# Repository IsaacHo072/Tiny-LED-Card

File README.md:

# Tiny LED Card
 A tiny credit card sized LED light

# Hardware
 Currently using 3030 LED and TPS61165 driver.
 
 Update 2022 Feb: It seems that you can't buy the TPS61165 anymore, all places are out of stock. 
 
 Update 2023: TPS61165 back in stock in most marketplace

## 3030 LED
 Luminus Device MP3030-110H
 
 Nominal: 3V 65mA
 
 Maximum: 200mA

## TPS61165
 Boost converter for LEDs in series

 Input voltage: 3-18V
 
 1.2A current limit

## PCB
 Aluminium PCB, single layer, for LED.
 
 FR-4 PCB, Two layers, for driver.
 Components on single side for easy assembly.
 
 2 PCBs connected with 2.54mm headers for upgradability 

## Enclosure
 3D Printed with PLA or any filament
 
 Screws: 4x M3x20
 
 2x M3x12-16mm 
 
# Assembly
 See the BOM for parts.
 Total cost should be under $25

 For the Aluminium PCB, you need a hotplate or a beefy hotair gun.
 It is impossible to solder with a soldering iron 
 
 For the driver PCB, any soldering iron will work, hotplate would also work well.
 
 R1 and R2 are the sense resistor for the LED driver, use the following resistor: 
  for other current see the datasheet of TPS61165
 
 | Resistor (Ω)  | LED Current (each) | Power | 
| ------------- | ------------- | ------------- |
| 1  | 50mA  | 14.4W |
| 0.5  | 100mA  | 28.8W |
| 0.33  | 150mA  | 43.2W |
| 0.25  | 200mA  | 57.6W |

 For the enclosure, print each file once and screw them together.
 
 Glue a heatsink with thermal adhesive at the back of the aluminium PCB after checked working.

## Usage
 Plug a 12V DC power supply in, light will come out from the bright side.
 
 It is not advised to use the Micro USB for power as a large amperage will be needed at 5V. Also, having both accidentally plugged in will damage the Micro USB device.

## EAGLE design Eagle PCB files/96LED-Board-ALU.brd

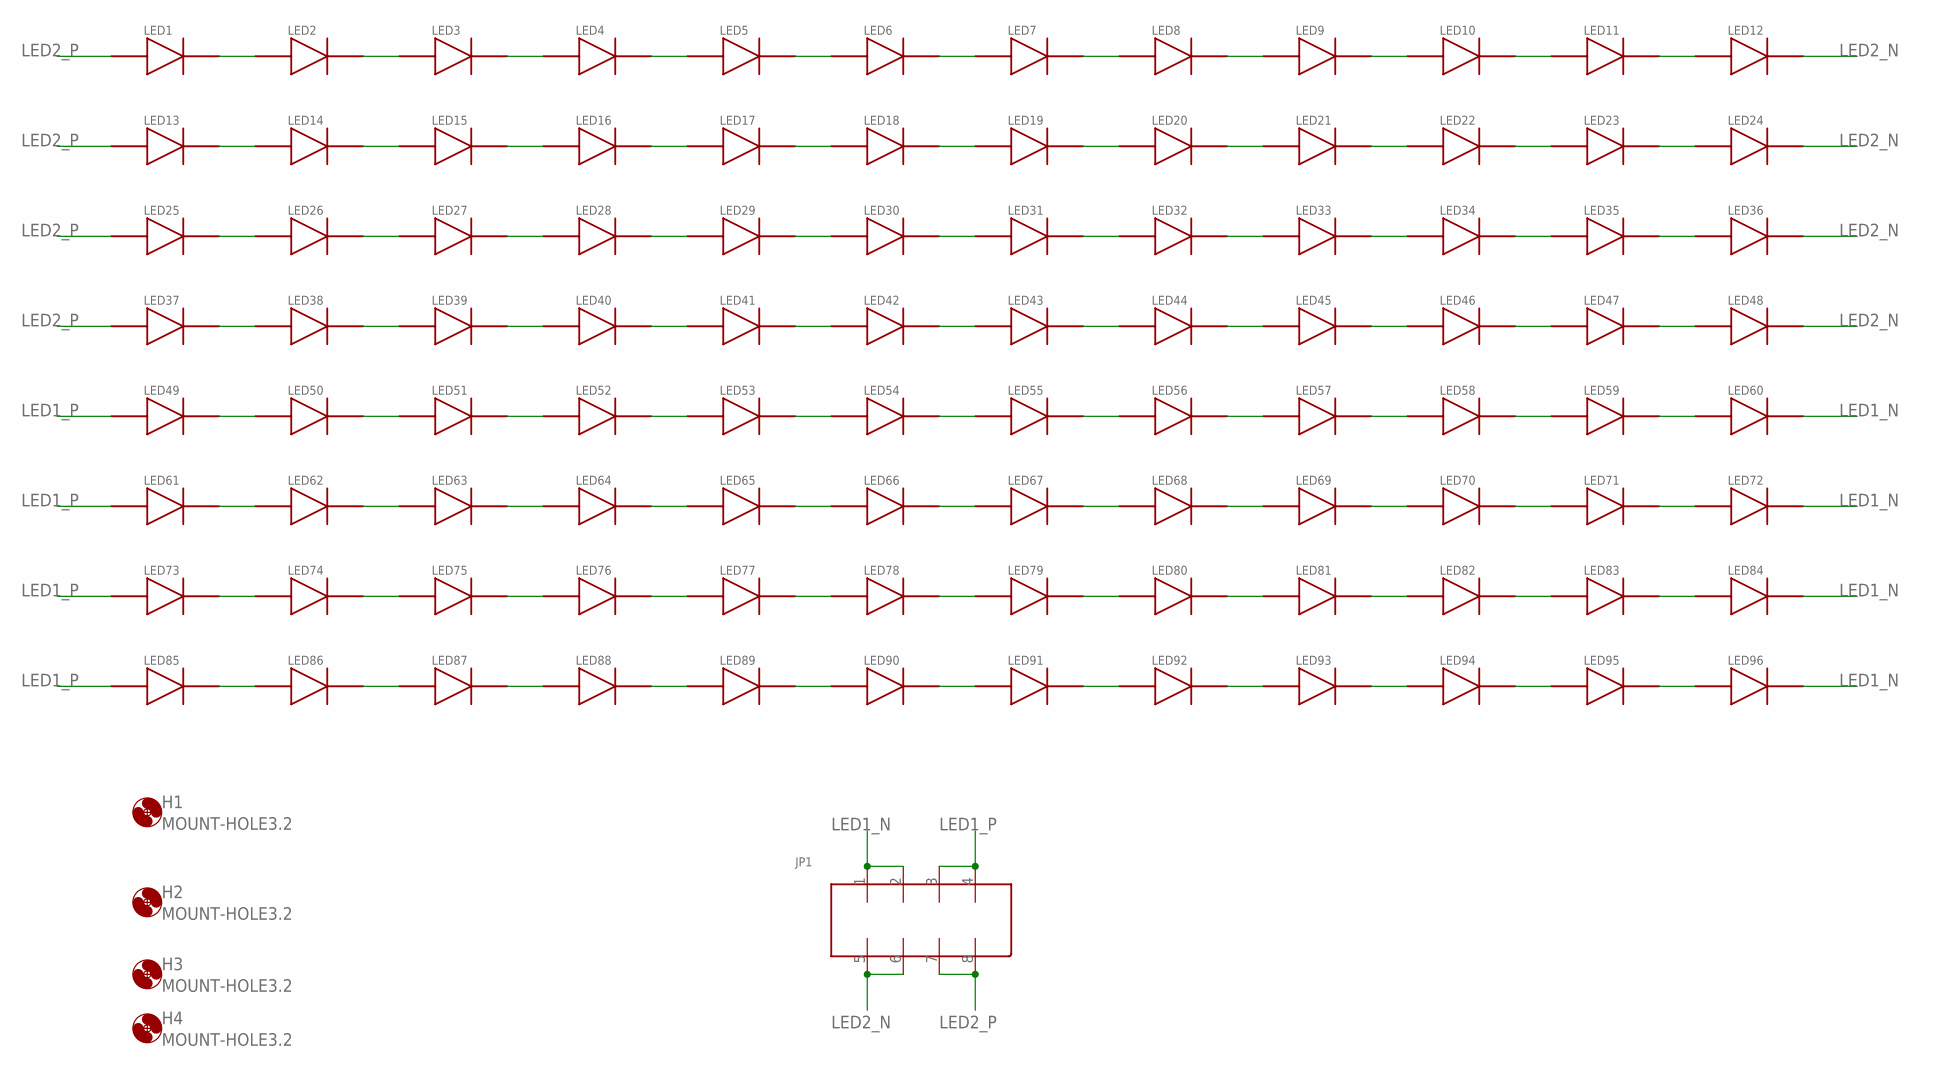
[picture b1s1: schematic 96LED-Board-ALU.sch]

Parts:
H1, H2, H3, H4: MOUNT-HOLE3.2; 3,2
JP1: 2X8P_2.54_FEMALE; 2X8_PIN_SMD_2.54-FEMALE
LED1, LED2, LED3, LED4, LED5, LED6, LED7, LED8, LED9, LED10, LED11, LED12, LED13, LED14, LED15, LED16, LED17, LED18, LED19, LED20, LED21, LED22, LED23, LED24, LED25, LED26, LED27, LED28, LED29, LED30, LED31, LED32, LED33, LED34, LED35, LED36, LED37, LED38, LED39, LED40, LED41, LED42, LED43, LED44, LED45, LED46, LED47, LED48, LED49, LED50, LED51, LED52, LED53, LED54, LED55, LED56, LED57, LED58, LED59, LED60, LED61, LED62, LED63, LED64, LED65, LED66, LED67, LED68, LED69, LED70, LED71, LED72, LED73, LED74, LED75, LED76, LED77, LED78, LED79, LED80, LED81, LED82, LED83, LED84, LED85, LED86, LED87, LED88, LED89, LED90, LED91, LED92, LED93, LED94, LED95, LED96: MP3030_N

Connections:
LED1_N: JP1.1, JP1.2, LED60.2, LED72.2, LED84.2, LED96.2
LED1_P: JP1.3, JP1.4, LED49.1, LED61.1, LED73.1, LED85.1
LED2_N: JP1.5, JP1.6, LED12.2, LED24.2, LED36.2, LED48.2
LED2_P: JP1.7, JP1.8, LED1.1, LED13.1, LED25.1, LED37.1
unnamed: LED1.2, LED2.1
unnamed: LED2.2, LED3.1
unnamed: LED3.2, LED4.1
unnamed: LED4.2, LED5.1
unnamed: LED5.2, LED6.1
unnamed: LED6.2, LED7.1
unnamed: LED7.2, LED8.1
unnamed: LED8.2, LED9.1
unnamed: LED9.2, LED10.1
unnamed: LED10.2, LED11.1
unnamed: LED11.2, LED12.1
unnamed: LED13.2, LED14.1
unnamed: LED14.2, LED15.1
unnamed: LED15.2, LED16.1
unnamed: LED16.2, LED17.1
unnamed: LED17.2, LED18.1
unnamed: LED18.2, LED19.1
unnamed: LED19.2, LED20.1
unnamed: LED20.2, LED21.1
unnamed: LED21.2, LED22.1
unnamed: LED22.2, LED23.1
unnamed: LED23.2, LED24.1
unnamed: LED25.2, LED26.1
unnamed: LED26.2, LED27.1
unnamed: LED27.2, LED28.1
unnamed: LED28.2, LED29.1
unnamed: LED29.2, LED30.1
unnamed: LED30.2, LED31.1
unnamed: LED31.2, LED32.1
unnamed: LED32.2, LED33.1
unnamed: LED33.2, LED34.1
unnamed: LED34.2, LED35.1
unnamed: LED35.2, LED36.1
unnamed: LED37.2, LED38.1
unnamed: LED38.2, LED39.1
unnamed: LED39.2, LED40.1
unnamed: LED40.2, LED41.1
unnamed: LED41.2, LED42.1
unnamed: LED42.2, LED43.1
unnamed: LED43.2, LED44.1
unnamed: LED44.2, LED45.1
unnamed: LED45.2, LED46.1
unnamed: LED46.2, LED47.1
unnamed: LED47.2, LED48.1
unnamed: LED49.2, LED50.1
unnamed: LED50.2, LED51.1
unnamed: LED51.2, LED52.1
unnamed: LED52.2, LED53.1
unnamed: LED53.2, LED54.1
unnamed: LED54.2, LED55.1
unnamed: LED55.2, LED56.1
unnamed: LED56.2, LED57.1
unnamed: LED57.2, LED58.1
unnamed: LED58.2, LED59.1
unnamed: LED59.2, LED60.1
unnamed: LED61.2, LED62.1
unnamed: LED62.2, LED63.1
unnamed: LED63.2, LED64.1
unnamed: LED64.2, LED65.1
unnamed: LED65.2, LED66.1
unnamed: LED66.2, LED67.1
unnamed: LED67.2, LED68.1
unnamed: LED68.2, LED69.1
unnamed: LED69.2, LED70.1
unnamed: LED70.2, LED71.1
unnamed: LED71.2, LED72.1
unnamed: LED73.2, LED74.1
unnamed: LED74.2, LED75.1
unnamed: LED75.2, LED76.1
unnamed: LED76.2, LED77.1
unnamed: LED77.2, LED78.1
unnamed: LED78.2, LED79.1
unnamed: LED79.2, LED80.1
unnamed: LED80.2, LED81.1
unnamed: LED81.2, LED82.1
unnamed: LED82.2, LED83.1
unnamed: LED83.2, LED84.1
unnamed: LED85.2, LED86.1
unnamed: LED86.2, LED87.1
unnamed: LED87.2, LED88.1
unnamed: LED88.2, LED89.1
unnamed: LED89.2, LED90.1
unnamed: LED90.2, LED91.1
unnamed: LED91.2, LED92.1
unnamed: LED92.2, LED93.1
unnamed: LED93.2, LED94.1
unnamed: LED94.2, LED95.1
unnamed: LED95.2, LED96.1

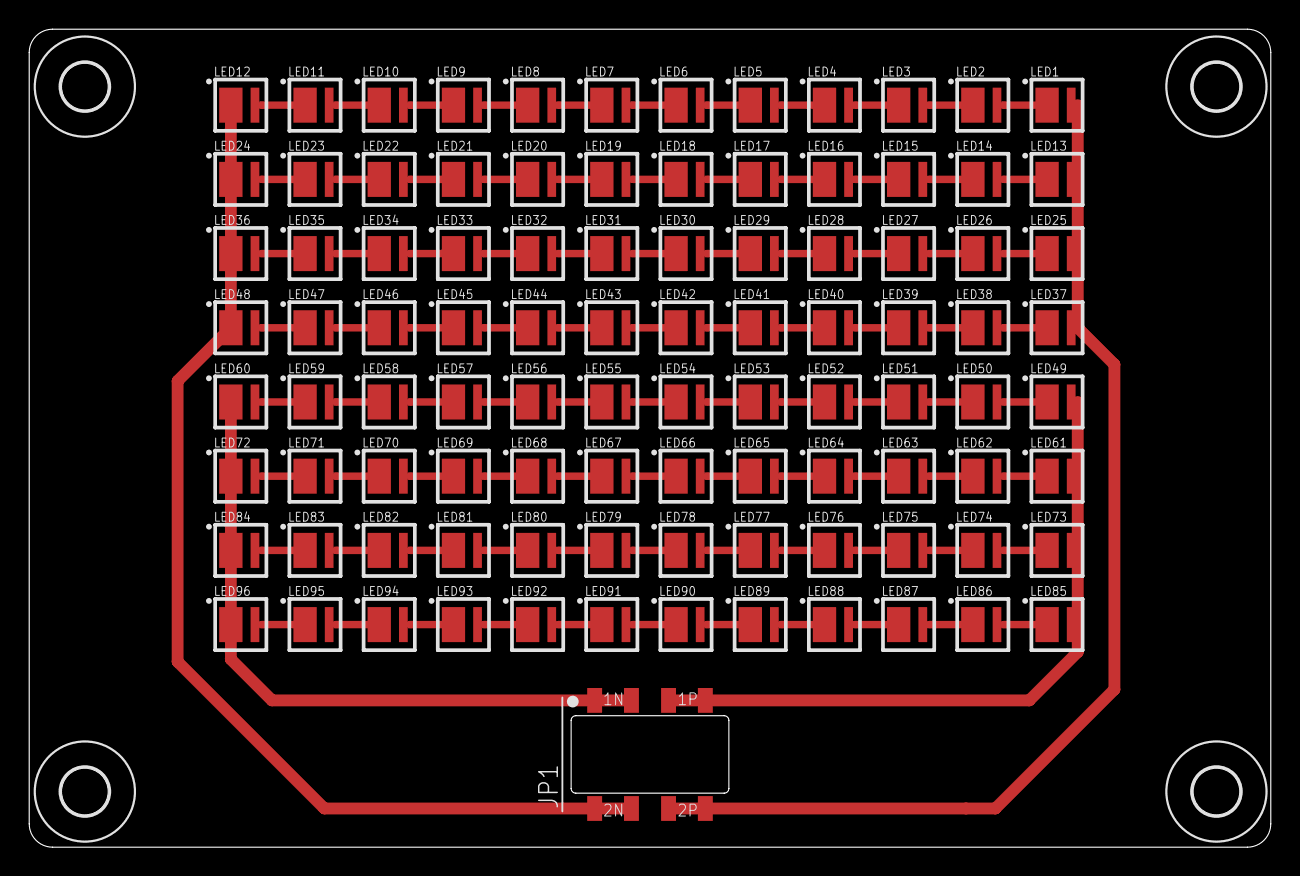
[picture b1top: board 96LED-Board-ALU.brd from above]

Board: 2 copper layers, 85.0 x 56.0 mm, 101 parts (0 on the bottom side), 92 nets.

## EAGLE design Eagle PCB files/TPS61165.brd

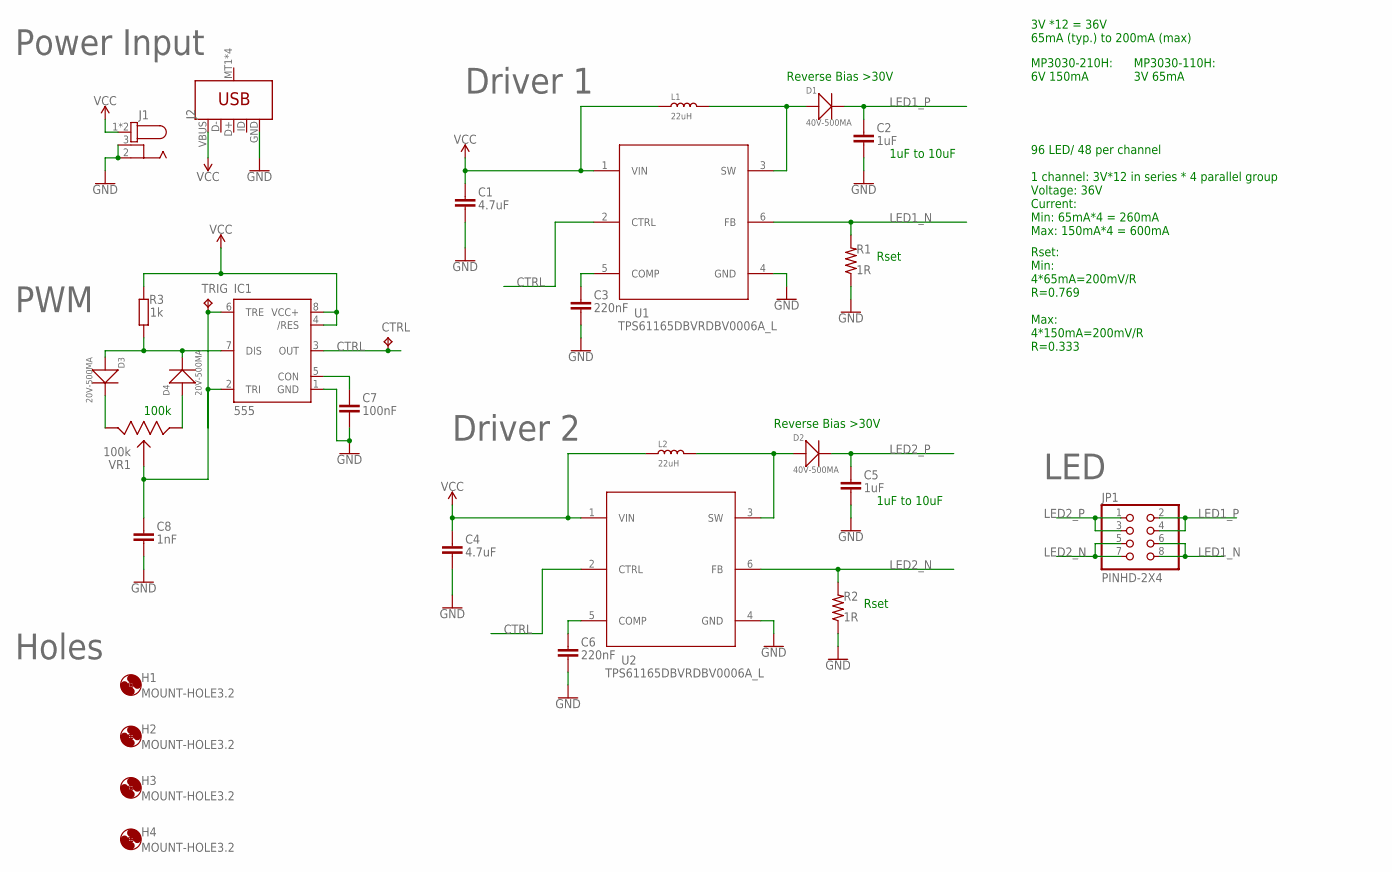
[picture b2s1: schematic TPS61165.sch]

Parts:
C1, C4: 4.7uF; CAPC2012X110
C2, C5: 1uF; CAPC2012X110
C3, C6: 220nF; CAPC1608X85
C7: 100nF; CAPC1608X85
C8: 1nF; CAPC1608X85
CTRL: TPB1,27; B1,27
D1, D2: 40V-500MA; SOD-123
D3, D4: 20V-500MA; SOD-123
H1, H2, H3, H4: MOUNT-HOLE3.2; 3,2
IC1: 555; SO08
J1: 694108106102
J2: USB_MICRO-B_SMT; USB-MICROB
JP1: PINHD-2X4; 2X04
L1, L2: 22uH; SMD-2P-L6.0XW6.0XH3.0MM
R1, R2: 1R; RESC3216X70
R3: 1k; RESC1608X60
TRIG: TPB1,27; B1,27
U1, U2: TPS61165DBVRDBV0006A_L; DBV0006A_L
VR1: 100k; B104-5PIN

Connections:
COMP: C3.1, U1.5 (COMP)
COMP1: C6.1, U2.5 (COMP)
CON: C7.1, IC1.5 (CON)
CTRL: CTRL.TP, IC1.3 (OUT), U1.2 (CTRL), U2.2 (CTRL)
DISCHARGE: D3.+, D4.-, IC1.7 (DIS), R3.1
GND: C1.2, C2.2, C3.2, C4.2, C5.2, C6.2, C7.2, C8.2, IC1.1 (GND), J1.2, J1.3, J2.GND, R1.1, R2.1, U1.4 (GND), U2.4 (GND)
LED1_N: JP1.6, JP1.8, R1.2, U1.6 (FB)
LED1_P: C2.1, D1.-, JP1.2, JP1.4
LED2_N: JP1.5, JP1.7, R2.2, U2.6 (FB)
LED2_P: C5.1, D2.-, JP1.1, JP1.3
unnamed: D3.-, VR1.P$3
unnamed: D4.+, VR1.P$1
SW: D1.+, L1.2, U1.3 (SW)
SW1: D2.+, L2.2, U2.3 (SW)
TRIGGER: C8.1, IC1.2 (TRI), IC1.6 (TRE), TRIG.TP, VR1.NOT_P$2
VCC: C1.1, C4.1, IC1.4 (/RES), IC1.8 (VCC+), J1.1, J1.A1 (1), J2.VBUS, L1.1, L2.1, R3.2, U1.1 (VIN), U2.1 (VIN)

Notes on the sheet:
MP3030-210H: 6V 150mA
MP3030-110H: 3V 65mA
Rset
1uF to 10uF
Reverse Bias >30V
3V *12 = 36V 65mA (typ.) to 200mA (max)
100k
Power Input
PWM
Driver 1
Driver 2
Holes
Rset: Min: 4*65mA=200mV/R R=0.769 Max: 4*150mA=200mV/R R=0.333
96 LED/ 48 per channel 1 channel: 3V*12 in series * 4 parallel group Voltage: 36V Current: Min: 65mA*4 = 260mA Max: 150mA*4 = 600mA
LED

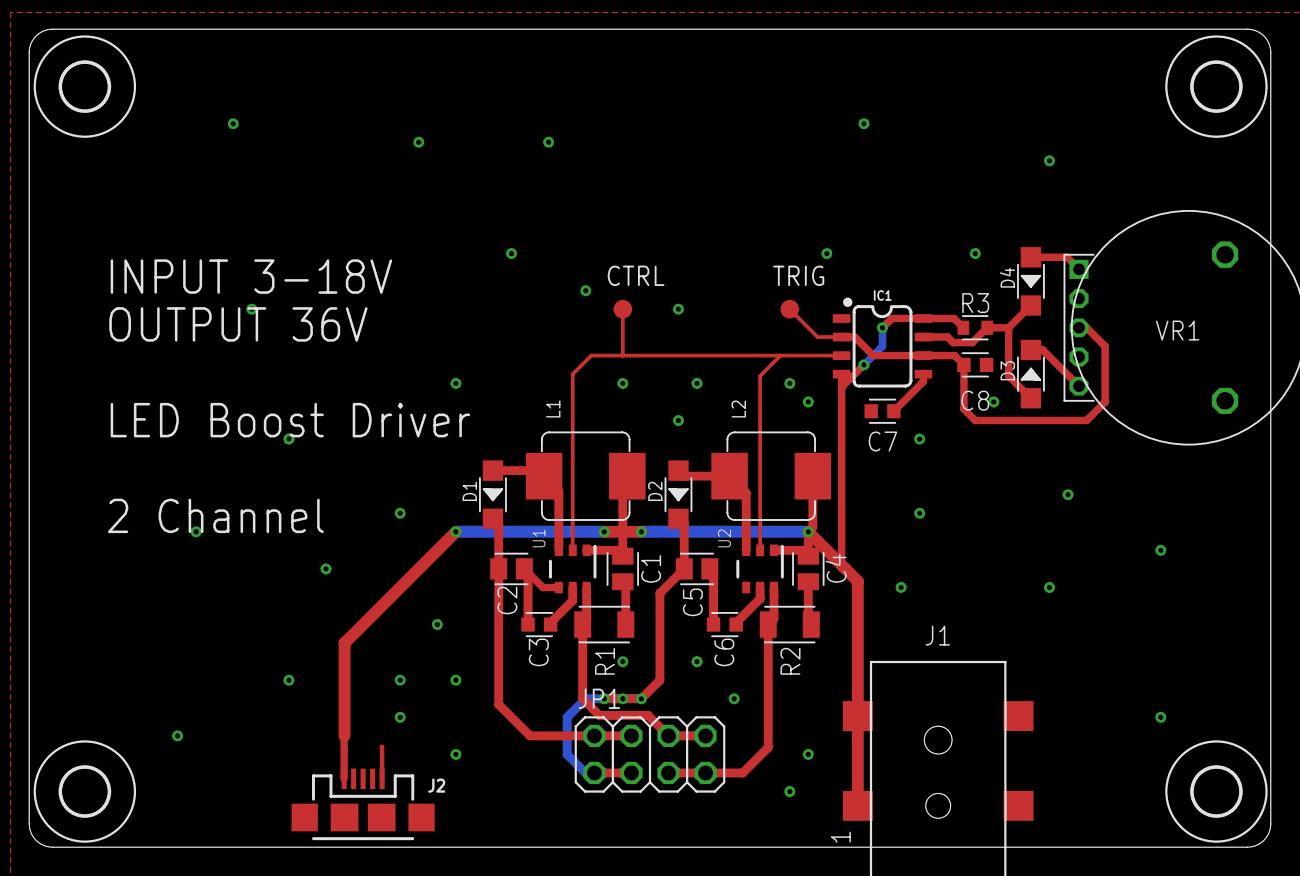
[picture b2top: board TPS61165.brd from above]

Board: 2 copper layers, 85.0 x 56.0 mm, 30 parts (0 on the bottom side), 16 nets.

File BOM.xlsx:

BOM
Driver
Part | Value | Package | CATEGORY | Remarks
C1 | 4.7uF | 0805 | Capacitor
C2 | 1uF | 0805 | Capacitor
C3 | 220nF | 0603 | Capacitor
C4 | 4.7uF | 0805 | Capacitor
C5 | 1uF | 0805 | Capacitor
C6 | 220nF | 0603 | Capacitor
C7 | 100nF | 0603 | Capacitor
C8 | 1nF | 0603 | Capacitor
D1 | 40V-500MA | SOD-123 | Diode
D2 | 40V-500MA | SOD-123 | Diode
D3 | 40V-500MA | SOD-123 | Diode
D4 | 40V-500MA | SOD-123 | Diode
H1 | MOUNT-HOLE3.2 | MOUNT-HOLE3.2 | Hole
H2 | MOUNT-HOLE3.2 | MOUNT-HOLE3.2 | Hole
H3 | MOUNT-HOLE3.2 | MOUNT-HOLE3.2 | Hole
H4 | MOUNT-HOLE3.2 | MOUNT-HOLE3.2 | Hole
IC1 | NE555 | SO08 | IC
J1 | DC5525 | SMD DC Power Jack | Connector
J2 |  | USB_MICRO-B_SMT |  | Not used
JP1 | PINHD-2X4 | PINHD-2X4 | Connector
L1 | 22uH | SMD-2P-L6.0XW6.0XH3.0MM
L2 | 22uH | SMD-2P-L6.0XW6.0XH3.0MM
R1 | 1R | 1206 | Resistor | Rset
R2 | 1R | 1206 | Resistor | Rset
R3 | 1k | 0603 | Resistor
U1 | TPS61165DBVR | SOT-23 | IC
U2 | TPS61165DBVR | SOT-23 | IC
VR1 | 100k | B104 (100K) 3 Pins | potentiometer
LED Board
LED1-96 | MP3030-110H | MP3030 | LED | Any 3V MP3030 LED could work
JP1 |  | SMD 2x4 | Connector | Sand the corners if it doesn’t fit

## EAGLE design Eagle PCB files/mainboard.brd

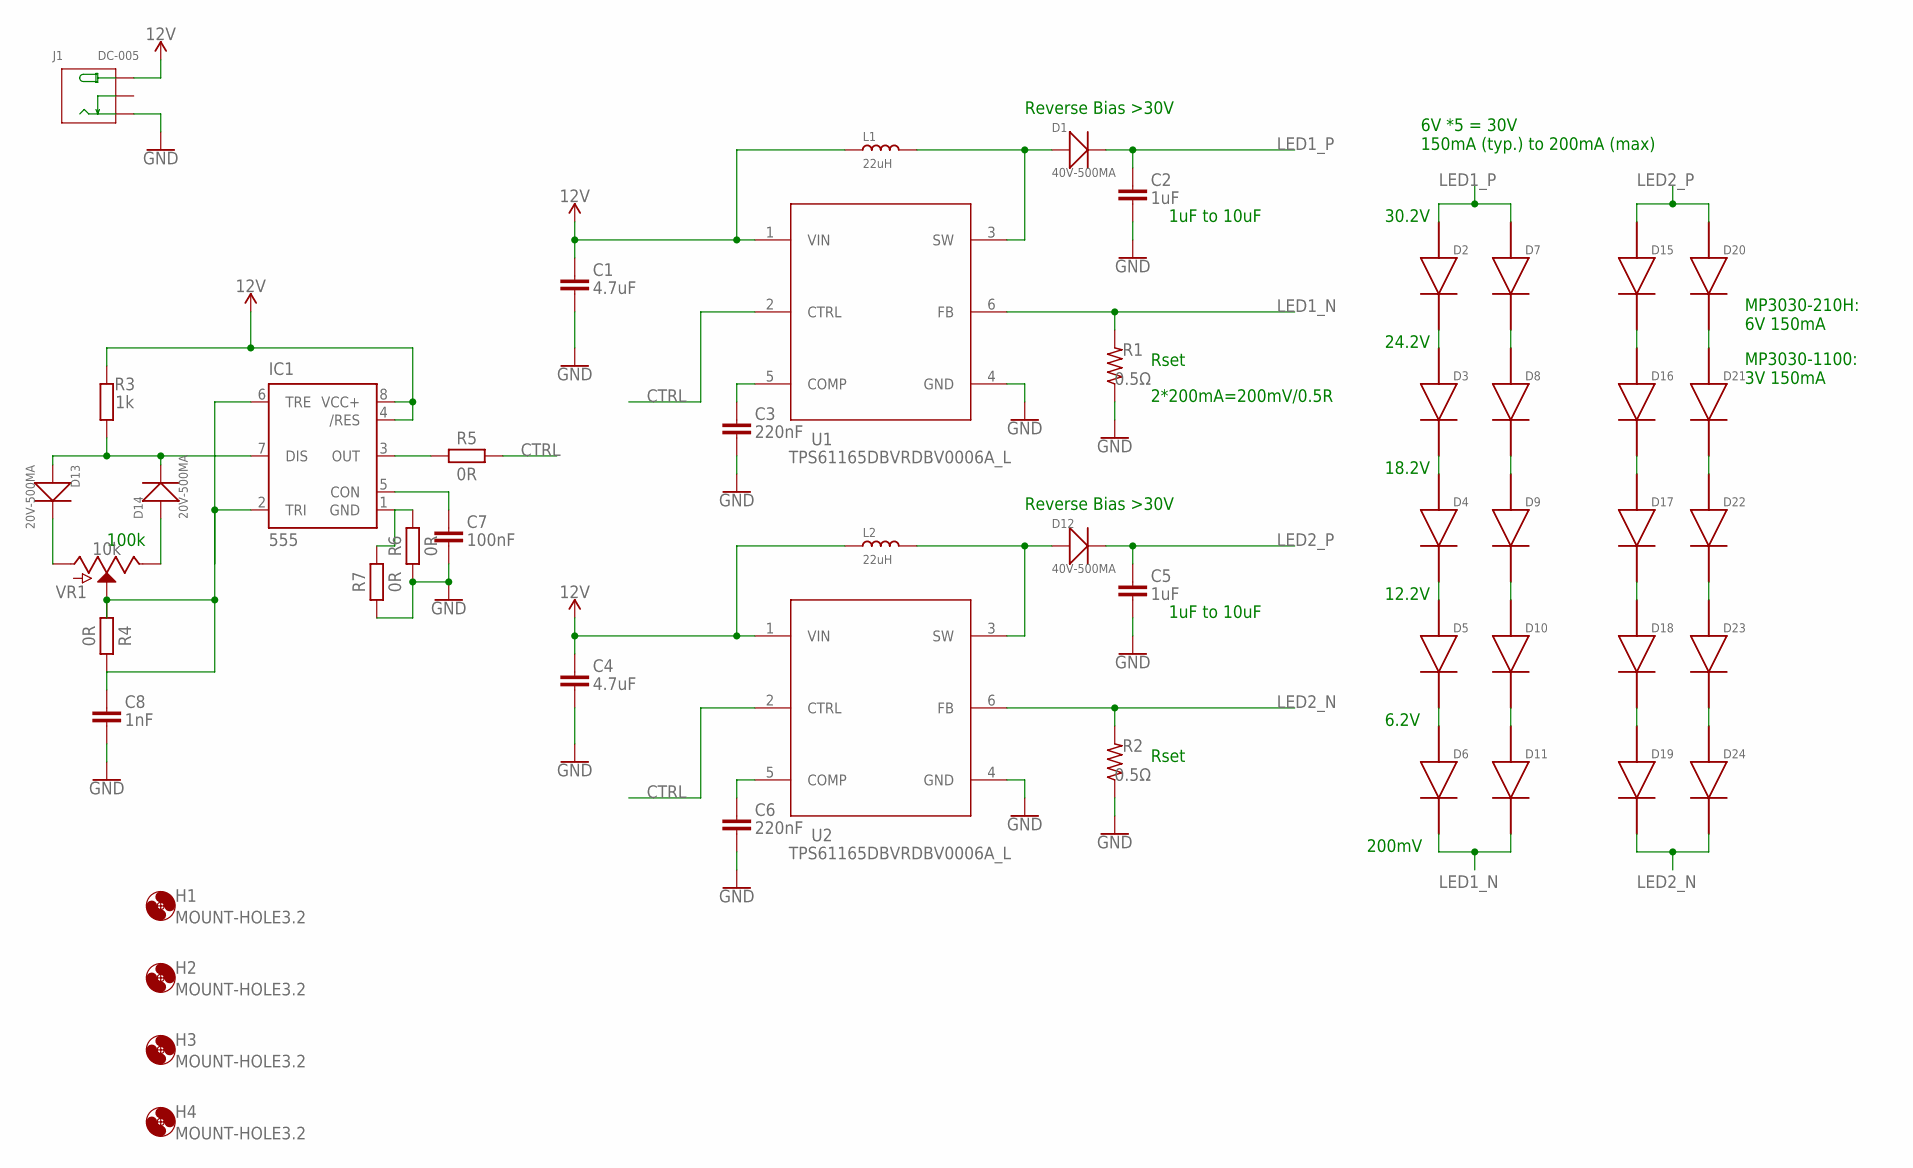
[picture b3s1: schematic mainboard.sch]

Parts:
C1, C4: 4.7uF; CAPC2012X110
C2, C5: 1uF; CAPC2012X110
C3, C6: 220nF; CAPC1608X85
C7: 100nF; CAPC1608X85
C8: 1nF; CAPC1608X85
D1, D12: 40V-500MA; SOD-123
D2, D3, D4, D5, D6, D7, D8, D9, D10, D11, D15, D16, D17, D18, D19, D20, D21, D22, D23, D24: MP3030_N
D13, D14: 20V-500MA; SOD-123
H1, H2, H3, H4: MOUNT-HOLE3.2; 3,2
IC1: 555; SO08
J1: DC-005; DCJ3P-14.2X11.0X9.0MM
L1, L2: 22uH; SMD-2P-L6.0XW6.0XH3.0MM
R1, R2: 0.5Ω; RESC3216X70
R3: 1k; RESC1608X60
R4, R5: 0R; RESC1608X60
R6, R7: 0R; RESC3216X70
U1, U2: TPS61165DBVRDBV0006A_L; DBV0006A_L
VR1: 10k; POT-PTH-ALPS

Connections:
12V: C1.1, C4.1, IC1.4 (/RES), IC1.8 (VCC+), J1.+B (+), J1.+T (+), L1.1, L2.1, R3.2, U1.1 (VIN), U2.1 (VIN)
COMP: C3.1, U1.5 (COMP)
COMP1: C6.1, U2.5 (COMP)
CON: C7.1, IC1.5 (CON)
CTRL: R5.2, U1.2 (CTRL), U2.2 (CTRL)
DISCHARGE: D13.+, D14.-, IC1.7 (DIS), R3.1
GND: C1.2, C2.2, C3.2, C4.2, C5.2, C6.2, C7.2, C8.2, IC1.1 (GND), J1.-1B (-), J1.-1T (-), R1.1, R2.1, R6.1, R6.2, R7.1, R7.2, U1.4 (GND), U2.4 (GND)
LED1_N: D6.2, D11.2, R1.2, U1.6 (FB)
LED1_P: C2.1, D1.-, D2.1, D7.1
LED2_N: D19.2, D24.2, R2.2, U2.6 (FB)
LED2_P: C5.1, D12.-, D15.1, D20.1
unnamed: D17.2, D18.1
unnamed: D2.2, D3.1
unnamed: D7.2, D8.1
unnamed: D3.2, D4.1
unnamed: D8.2, D9.1
unnamed: D4.2, D5.1
unnamed: D9.2, D10.1
unnamed: D5.2, D6.1
unnamed: D13.-, VR1.P$3 (A)
unnamed: D14.+, VR1.P$1 (E)
unnamed: D10.2, D11.1
unnamed: IC1.3 (OUT), R5.1
unnamed: D15.2, D16.1
unnamed: D16.2, D17.1
unnamed: D18.2, D19.1
unnamed: D23.2, D24.1
unnamed: D22.2, D23.1
unnamed: D21.2, D22.1
unnamed: D20.2, D21.1
SW: D1.+, L1.2, U1.3 (SW)
SW1: D12.+, L2.2, U2.3 (SW)
TRIGGER: C8.1, IC1.2 (TRI), IC1.6 (TRE), R4.1, R4.2, VR1.P$2 (S)

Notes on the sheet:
MP3030-210H: 6V 150mA
MP3030-1100: 3V 150mA
Rset
1uF to 10uF
Reverse Bias >30V
6V *5 = 30V 150mA (typ.) to 200mA (max)
100k
200mV
6.2V
12.2V
18.2V
24.2V
30.2V
2*200mA=200mV/0.5R

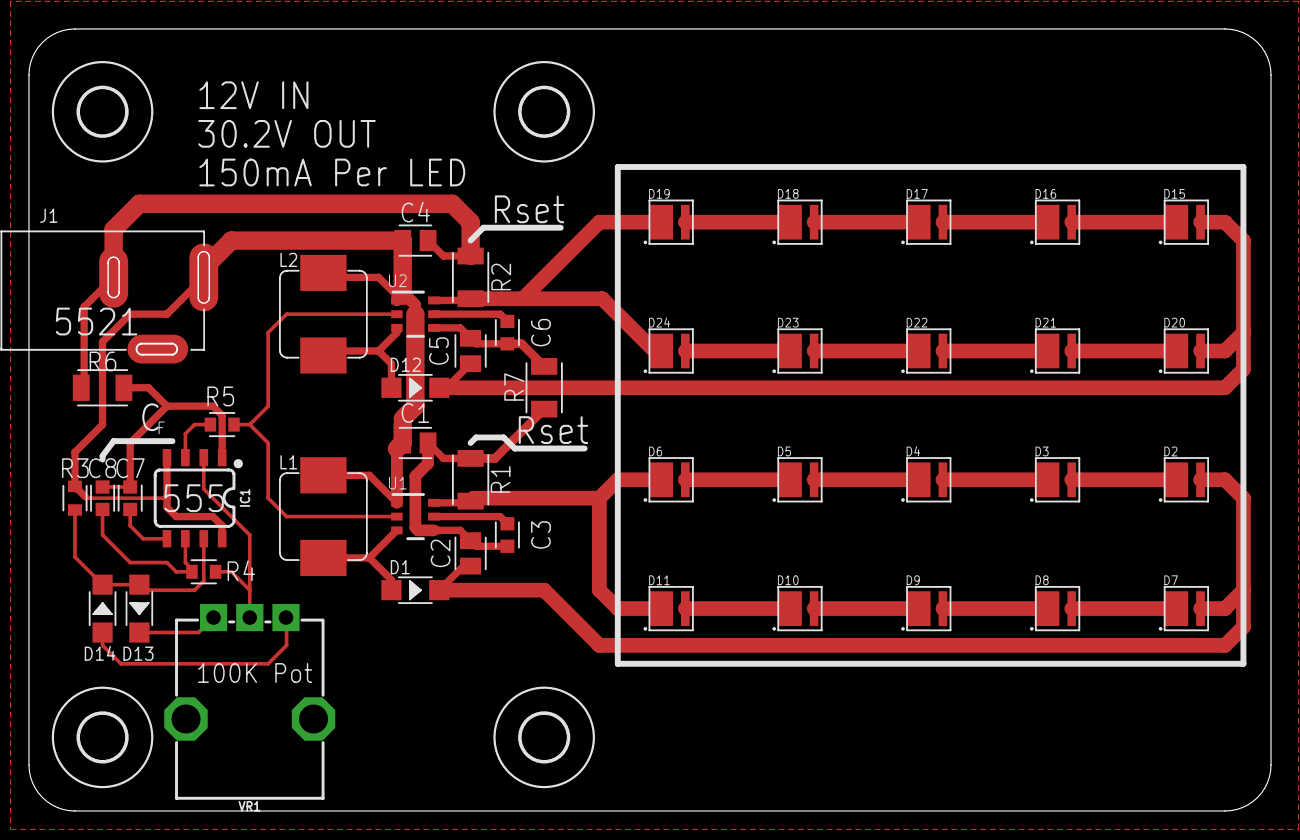
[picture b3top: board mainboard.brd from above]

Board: 2 copper layers, 85.7 x 54.0 mm, 50 parts (0 on the bottom side), 33 nets.

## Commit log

2021-08-30 Update Eagle files
2021-09-22 Updated PCB files
2021-09-22 Added Enclosure STL
2021-09-22 Added Pictures
2021-09-22 Added BOM file
2021-09-22 Changed picture file name
2023-10-31 Update README.md
    linebreak

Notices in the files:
parts and their libraries:
SparkFun-Aesthetics: Licensing: Creative Commons ShareAlike 4.0 International - https://creativecommons.org/licenses/by-sa/4.0
COPYRIGHT: Copyright (C) 2021 Ultra Librarian. All rights reserved.
